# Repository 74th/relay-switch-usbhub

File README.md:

# Relay Switch USB 2.0 Hub

This is a USB hub with USB switching function using relays.

Many existing USB hubs with USB host switching function only allow 2-port switching, and I made this kit because we wanted a 4-port hub.
Since there are no USB hubs using USB Type-C available on the market, it is convenient to use USB Type-C.
Since I wanted to place the USB hub behind the display, we also added the ability to switch remotely using a Grove cable.

Usually a dedicated USB switching IC should be used for USB switching, but this is achieved by using a relay to switch between DM/DP. It works by me, so I am not guaranteeing that it works, but I am publishing it.

リレーを使った USB 切り替え機能付き USB ハブです。

既存の USB ホスト切り替え機能付き USB ハブでは、多くが 2 ポートしか切り替えられず、4 ポートが欲しかったため作りました。
USB Type-C を使った USB ハブは販売されていないため、USB Type-C が使えると便利です。
USB ハブはディスプレイの裏に置きたかったため、Grove ケーブルを使ってリモートから切り替えられる機能もつけました。

本来は USB 切り替えには USB 切り替え専用の IC を使うべきですが、これはリレーを使って DM/DP を切り替えることで実現しています。私の所では動作しているので、動作は保証しませんが、公開しています。

> Shop [BOOTH](https://74th.booth.pm/items/5080690)

## features

- Switch between 4 USB Hosts with Relay
- 4-port USB 2.0 hub using CH334
- MX compatible DIY keyboard switches can be used to switch between USB hosts
- Currently enabled USB host is indicated by LED color
- A Grove cable can be used to place a USB host switching switch at a remote location
- Power protection IC on both USB device and USB host side
- USB port next to LED for power supply
- All USB ports are Type-C

### Japanese

- リレーを使った USB ホスト切り替え機能
- CH334 を使った 4 ポート USB 2.0 ハブ
- USB ホストの切り替えスイッチには MX 互換自作キーボードスイッチが使える
- 現在有効な USB ホストを LED の色で表示する
- Grove ケーブルで、離れた位置に USB ホストを切り替えるスイッチを置くことができる
- USB デバイス、USB ホスト側の両方に電源保護 IC を搭載
- LED 横の USB ポートは電源供給用
- 全ての USB ポートは Type-C

## Repository Structure

- Relay USB Hub
  - PCB KiCad Data: [./main-pcb](./main-pcb)
  - Relay Control MCU Firmware(CH32V003F6P6): [./main-firmware](./main-firmware)
  - Case 3D Printer Model(WIP): [./case/case-bottom.stl](./case/case-bottom.stl)
- Button Unit Grove I2C
  - PCB KiCad Data: [./remote_switch-pcb](./remote_switch-pcb)
  - Button Unit MCU Firmware(CH32V003F6P6): [./remote_switch-firmware](./remote_switch-firmware)
  - Case 3D Printer Model(WIP): [./case/remote-bottom.stl](./case/remote-bottom.stl)

## About Using IC

- CH334R: USB 2.0 Hub controller IC
  - Product Site: https://www.wch-ic.com/products/CH334.html
  - Datasheet: https://www.wch-ic.com/downloads/CH334DS0_PDF.html
- CH32V003: Low Cost General Purpose MCU
  - Product Site: https://www.wch-ic.com/products/CH32V003.html
  - Datasheet: https://www.wch-ic.com/downloads/CH32V003DS0_PDF.html

## Relay USB Hub v1.0.1

- Semantics: [PDF](./main-pcb/relay_usb_switch_hub-v1.0.1-semantics.pdf) [Kicanvas](https://kicanvas.org/?github=https%3A%2F%2Fgithub.com%2F74th%2Frelay-switch-usbhub%2Fblob%2Fmain%2F1.0.1%2Fpcb%2Fusb_relay_hub.kicad_sch)
- PCB: [Kicanvas](https://kicanvas.org/?github=https%3A%2F%2Fgithub.com%2F74th%2Frelay-switch-usbhub%2Fblob%2Fmain%2F1.0.1%2Fpcb%2Fusb_relay_hub.kicad_pcb)

### BOM

| Reference          | Name                                             | Quantity |
| ------------------ | ------------------------------------------------ | -------- |
| C1, C3-C6, C8, C12 | Capacitor 0603 10uF                              | 7        |
| C2, C11            | Capacitor 0603 100nF                             | 2        |
| C7                 | NC                                               | 1        |
| C9, C10            | Capacitor 0603 20-22pF                           | 2        |
| CH2                | HY2.0 Socket SMD 4Pin - I2C                      | 1        |
| D1                 | RGBLED WS2812B                                   | 1        |
| D2-D5              | Fast Switching Diode SOD-123 1N4148W             | 4        |
| J1-J4              | USB Type-C Receptacle - USB Device               | 4        |
| J5                 | USB Type-C Receptacle - Power                    | 1        |
| J6-J9              | USB Type-C Receptacle - Com Host                 | 4        |
| K1-K4              | 5V 2 Form C Relay                                | 4        |
| R1-R10             | Register 0603 5.1kΩ                              | 10       |
| R11                | Register 0603 27Ω                                | 1        |
| R12                | Register 0603 10kΩ                               | 1        |
| R13-R20, R23-R26   | Register 0603 56kΩ                               | 12       |
| R21, R22           | Register 0603 1kΩ                                | 2        |
| SW1-SW4            | Cherry MX Compatible Switch or Kailh Choc Switch | 4        |
| U1-U4              | USB Power Protection IC SOT-23 CH213K            | 4        |
| U6                 | MCU LQFP48 WCH CH32V003F4P6                      | 1        |
| U7-U10             | USB Power Protection IC SOT-23-6L CH217K         | 4        |
| U11                | USB 2.0 Hub Controller QSOP-16 CH334R            | 1        |
| Y1                 | Crystal 3225 12MHz                               | 1        |

## Button Unit Grove v1.0.0

- Semantics: [PDF](./remote_switch-pcb/button_unit_grove_i2c-v1.0.0-semantics.pdf) [Kicanvas](https://kicanvas.org/?github=https%3A%2F%2Fgithub.com%2F74th%2Frelay-switch-usbhub%2Fblob%2Fbutton_unit_grove_i2c%2F1.0.0%2Fswitch-pcb%2Fswitch-pcb.kicad_sch)
- PCB: [Kicanvas](https://kicanvas.org/?github=https%3A%2F%2Fgithub.com%2F74th%2Frelay-switch-usbhub%2Fblob%2Fbutton_unit_grove_i2c%2F1.0.0%2Fswitch-pcb%2Fswitch-pcb.kicad_pcb)

### BOM

| Reference | Name                                             | Quantity |
| --------- | ------------------------------------------------ | -------- |
| C1        | Capacitor 0805 100nF                             | 1        |
| C2        | Capacitor 0805 10uF                              | 1        |
| CH1       | HY2.0 Socket SMD 4Pin - Grove I2C                | 1        |
| D1-D4     | RGBLED 3528 SK6812MINI-E                         | 4        |
| R1        | Register 0805 10kΩ                               | 1        |
| R2        | Register 0805 27Ω                                | 1        |
| SW1-SW4   | Cherry MX Compatible Switch or Kailh Choc Switch | 4        |
| U1        | MCU LQFP48 WCH CH32V003F4P6                      | 1        |

## License

MIT

日本では販売しないでいただけるとありがたいです。

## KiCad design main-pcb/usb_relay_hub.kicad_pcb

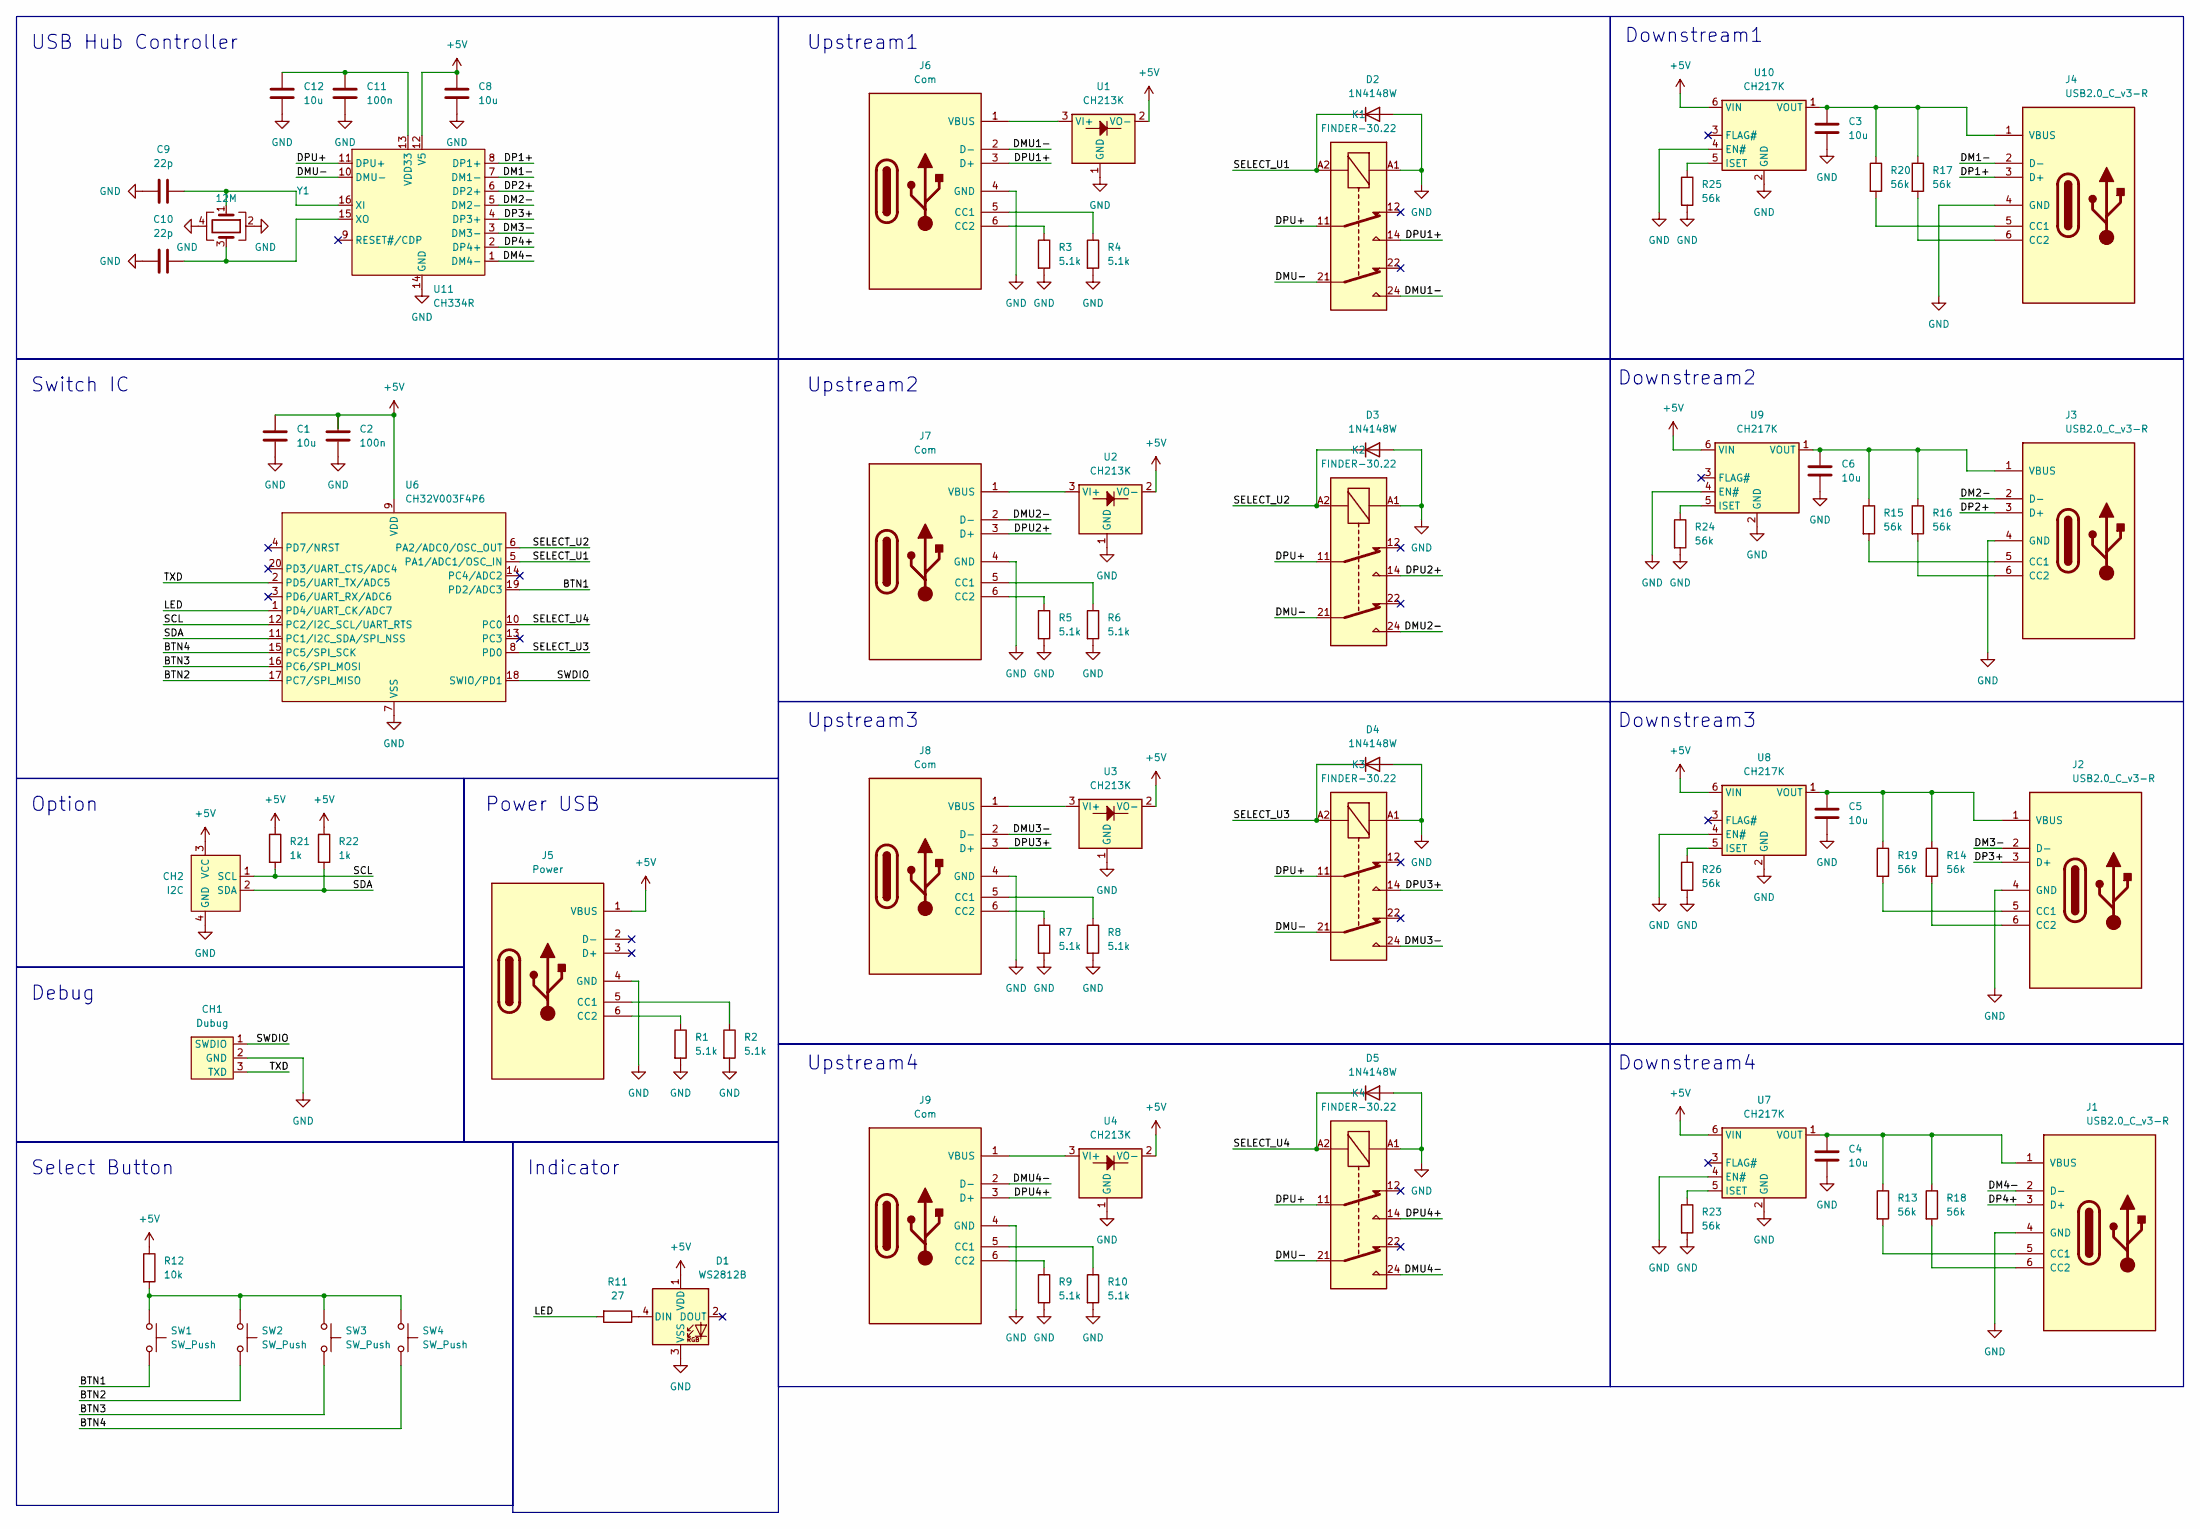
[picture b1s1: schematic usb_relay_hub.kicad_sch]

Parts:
C1, C3, C4, C5, C6, C8, C12: 10u; Capacitor_0603_1608
C2, C11: 100n; Capacitor_0603_1608
C9, C10: 22p; Capacitor_0603_1608
CH1: Dubug; CH32V003-DebugPort
CH2: I2C; HY2.0_Socket_SMD_4Pin
D1: WS2812B; LED_WS2812B_PLCC4_5.0x5.0mm_P3.2mm
D2, D3, D4, D5: 1N4148W; D_SOD-123
J1, J2, J3, J4: USB2.0_C_v3-R; USB-C-12-Pin-MidMount-ali-v5
J5: Power; USB-C-12-Pin-MidMount-ali-v5
J6, J7, J8, J9: Com; USB-C-12-Pin-MidMount-ali-v5
K1, K2, K3, K4: FINDER-30.22; Relay_DPDT_Finder_30.22
R1, R2, R3, R4, R5, R6, R7, R8, R9, R10: 5.1k; Register_0603_1608
R11: 27; Register_0603_1608
R12: 10k; Register_0603_1608
R13, R14, R15, R16, R17, R18, R19, R20, R23, R24, R25, R26: 56k; Register_0603_1608
R21, R22: 1k; Register_0603_1608
SW1, SW2, SW3, SW4: SW_Push; MXChocDirect_1Side_1.0u
U1, U2, U3, U4: CH213K; SOT-23
U6: CH32V003F4P6; TSSOP-20_4.4x6.5mm_P0.65mm
U7, U8, U9, U10: CH217K; SOT-23-6
U11: CH334R; QSOP-16_3.9x4.9mm_P0.635mm
Y1: 12M; Crystal_SMD_3225-4Pin_3.2x2.5mm_HandSoldering

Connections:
+5V: C1.1, C2.1, C8.1, CH2.3 (VCC), D1.1 (VDD), J5.1 (VBUS), R12.1, R21.1, R22.1, U1.2 (VO-), U2.2 (VO-), U3.2 (VO-), U4.2 (VO-), U6.9 (VDD), U7.6 (VIN), U8.6 (VIN), U9.6 (VIN), U10.6 (VIN), U11.12 (V5); also elsewhere on the board
/BTN1: SW1.2, U6.19 (PD2/ADC3)
/BTN2: SW2.2, U6.17 (PC7/SPI_MISO)
/BTN3: SW3.2, U6.16 (PC6/SPI_MOSI)
/BTN4: SW4.2, U6.15 (PC5/SPI_SCK)
/DM1-: J4.2 (D-), U11.7 (DM1-)
/DM2-: J3.2 (D-), U11.5 (DM2-)
/DM3-: J2.2 (D-), U11.3 (DM3-)
/DM4-: J1.2 (D-), U11.1 (DM4-)
/DMU1-: J6.2 (D-), K1.24
/DMU2-: J7.2 (D-), K2.24
/DMU3-: J8.2 (D-), K3.24
/DMU4-: J9.2 (D-), K4.24
/DMU-: K1.21, K2.21, K3.21, K4.21, U11.10 (DMU-)
/DP1+: J4.3 (D+), U11.8 (DP1+)
/DP2+: J3.3 (D+), U11.6 (DP2+)
/DP3+: J2.3 (D+), U11.4 (DP3+)
/DP4+: J1.3 (D+), U11.2 (DP4+)
/DPU1+: J6.3 (D+), K1.14
/DPU2+: J7.3 (D+), K2.14
/DPU3+: J8.3 (D+), K3.14
/DPU4+: J9.3 (D+), K4.14
/DPU+: K1.11, K2.11, K3.11, K4.11, U11.11 (DPU+)
/LED: R11.2, U6.1 (PD4/UART_CK/ADC7)
/SCL: CH2.1 (SCL), R21.2, U6.12 (PC2/I2C_SCL/UART_RTS)
/SDA: CH2.2 (SDA), R22.2, U6.11 (PC1/I2C_SDA/SPI_NSS)
/SELECT_U1: D2.1 (K), K1.A2, U6.5 (PA1/ADC1/OSC_IN)
/SELECT_U2: D3.1 (K), K2.A2, U6.6 (PA2/ADC0/OSC_OUT)
/SELECT_U3: D4.1 (K), K3.A2, U6.8 (PD0)
/SELECT_U4: D5.1 (K), K4.A2, U6.10 (PC0)
/SWDIO: CH1.1 (SWDIO), U6.18 (SWIO/PD1)
/TXD: CH1.3 (TXD), U6.2 (PD5/UART_TX/ADC5)
GND: C1.2, C2.2, C3.2, C4.2, C5.2, C6.2, C8.2, C9.2, C10.1, C11.2, C12.2, CH1.2 (GND), CH2.4 (GND), D1.3 (VSS), D2.2 (A), D3.2 (A), D4.2 (A), D5.2 (A), J1.4 (GND), J2.4 (GND), J3.4 (GND), J4.4 (GND), J5.4 (GND), J6.4 (GND), J7.4 (GND), J8.4 (GND), J9.4 (GND), K1.A1, K2.A1, K3.A1, K4.A1, R1.2, R2.2, R3.2, R4.2, R5.2, R6.2, R7.2, R8.2, R9.2, R10.2, R23.2, R24.2, R25.2, R26.2, U1.1 (GND), U2.1 (GND), U3.1 (GND), U4.1 (GND), U6.7 (VSS), U7.2 (GND), U7.4 (EN#), U8.2 (GND), U8.4 (EN#), U9.2 (GND), U9.4 (EN#), U10.2 (GND), U10.4 (EN#), U11.14 (GND), Y1.2, Y1.4; also elsewhere on the board
unnamed: D1.4 (DIN), R11.1
unnamed: J1.5 (CC1), R13.2
unnamed: J1.6 (CC2), R18.2
unnamed: C4.1, J1.1 (VBUS), R13.1, R18.1, U7.1 (VOUT)
unnamed: J2.5 (CC1), R19.2
unnamed: J2.6 (CC2), R14.2
unnamed: C5.1, J2.1 (VBUS), R14.1, R19.1, U8.1 (VOUT)
unnamed: J3.5 (CC1), R15.2
unnamed: J3.6 (CC2), R16.2
unnamed: C6.1, J3.1 (VBUS), R15.1, R16.1, U9.1 (VOUT)
unnamed: J4.5 (CC1), R20.2
unnamed: J4.6 (CC2), R17.2
unnamed: C3.1, J4.1 (VBUS), R17.1, R20.1, U10.1 (VOUT)
unnamed: J5.5 (CC1), R2.1
unnamed: J5.6 (CC2), R1.1
unnamed: J6.5 (CC1), R4.1
unnamed: J6.6 (CC2), R3.1
unnamed: J6.1 (VBUS), U1.3 (VI+)
unnamed: J7.5 (CC1), R6.1
unnamed: J7.6 (CC2), R5.1
unnamed: J7.1 (VBUS), U2.3 (VI+)
unnamed: J8.5 (CC1), R8.1
unnamed: J8.6 (CC2), R7.1
unnamed: J8.1 (VBUS), U3.3 (VI+)
unnamed: J9.5 (CC1), R10.1
unnamed: J9.6 (CC2), R9.1
unnamed: J9.1 (VBUS), U4.3 (VI+)
unnamed: R12.2, SW1.1, SW2.1, SW3.1, SW4.1
unnamed: R23.1, U7.5 (ISET)
unnamed: R26.1, U8.5 (ISET)
unnamed: R24.1, U9.5 (ISET)
unnamed: R25.1, U10.5 (ISET)
unnamed: C11.1, C12.1, U11.13 (VDD33)
unnamed: C9.1, U11.16 (XI), Y1.1
unnamed: C10.2, U11.15 (XO), Y1.3

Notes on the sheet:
Switch IC
Debug
Upstream2
Downstream1
Select Button
Power USB
Upstream1
Upstream4
Indicator
Downstream3
USB Hub Controller
Downstream4
Option
Downstream2
Upstream3

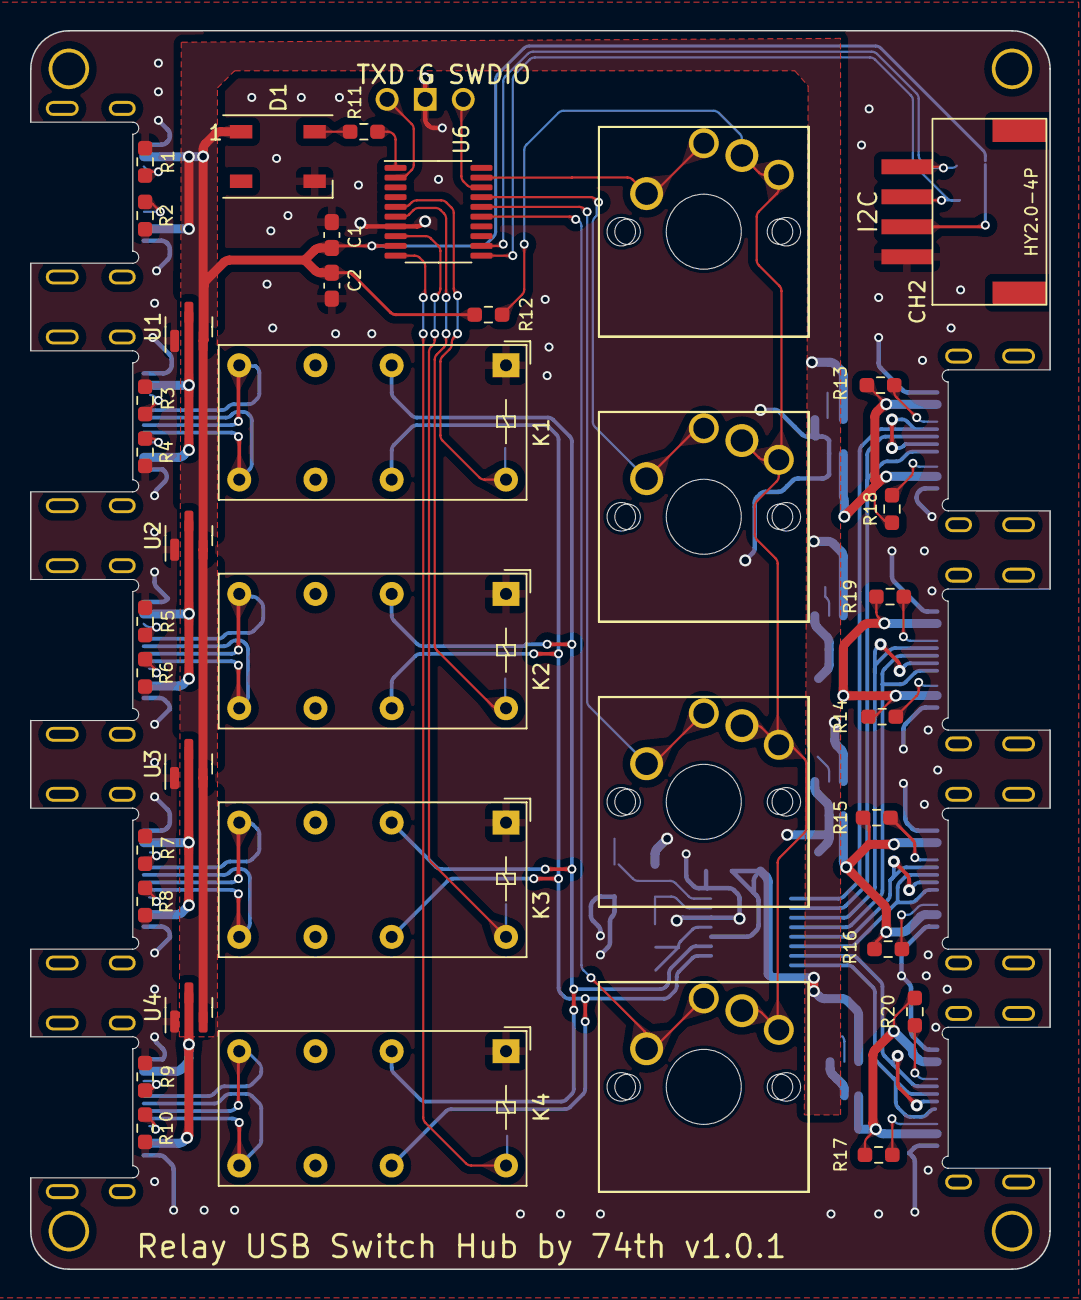
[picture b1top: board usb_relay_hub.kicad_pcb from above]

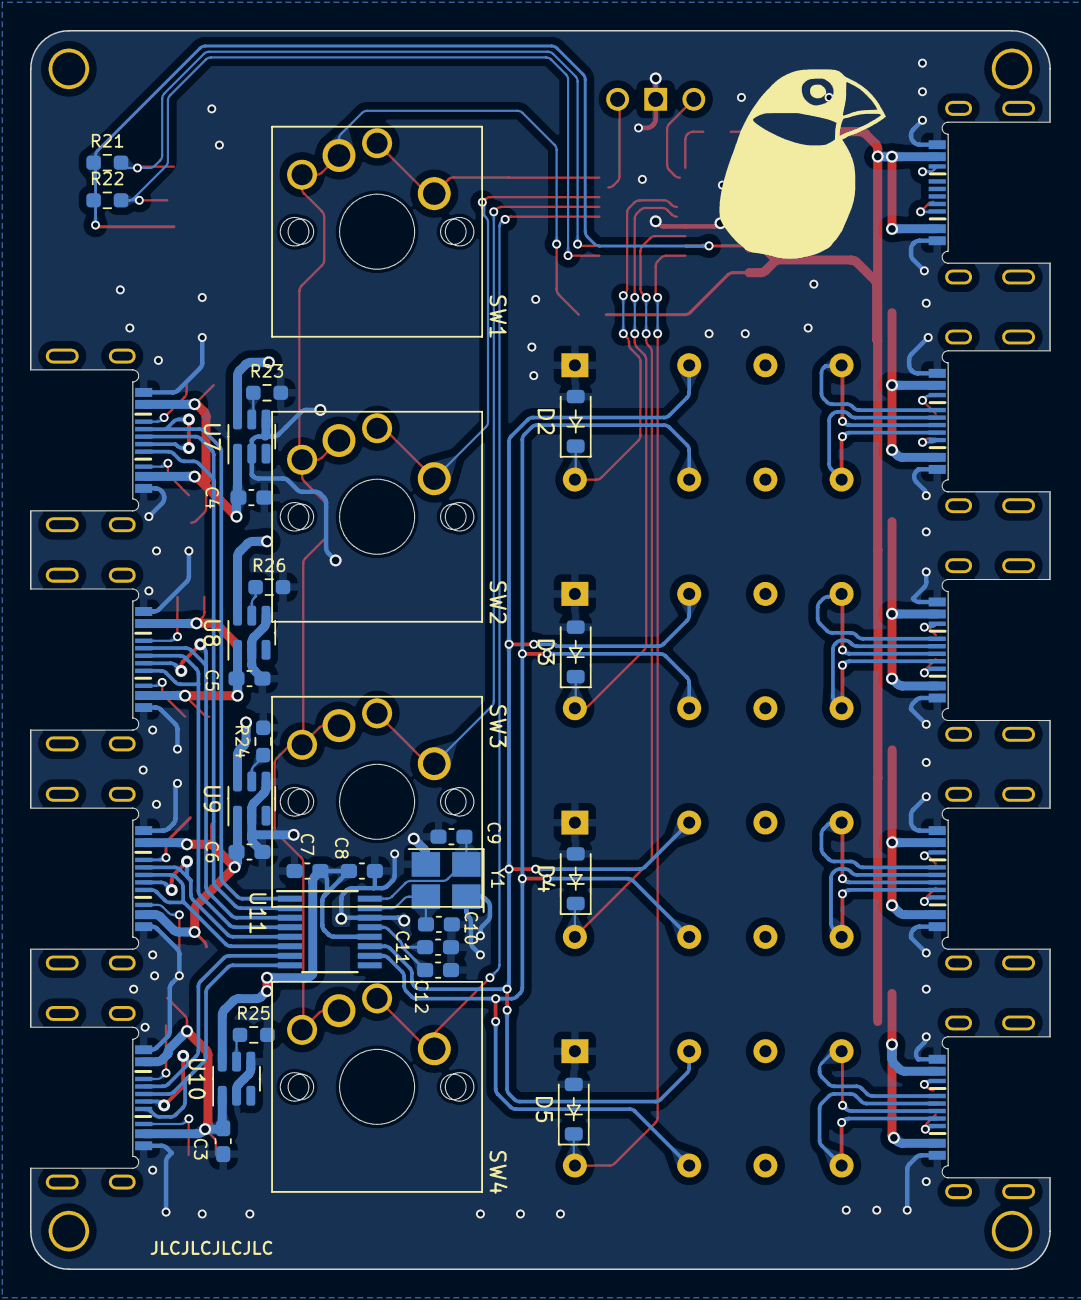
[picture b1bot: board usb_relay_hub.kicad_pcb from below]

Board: 2 copper layers, 67.9 x 82.5 mm, 77 parts (35 on the bottom side), 68 nets.

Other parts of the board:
C7: 100n; Capacitor_0603_1608
M1, M2, M3, M4: M2_v2

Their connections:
+5V: C7.1; also elsewhere on the board
GND: C7.2; also elsewhere on the board

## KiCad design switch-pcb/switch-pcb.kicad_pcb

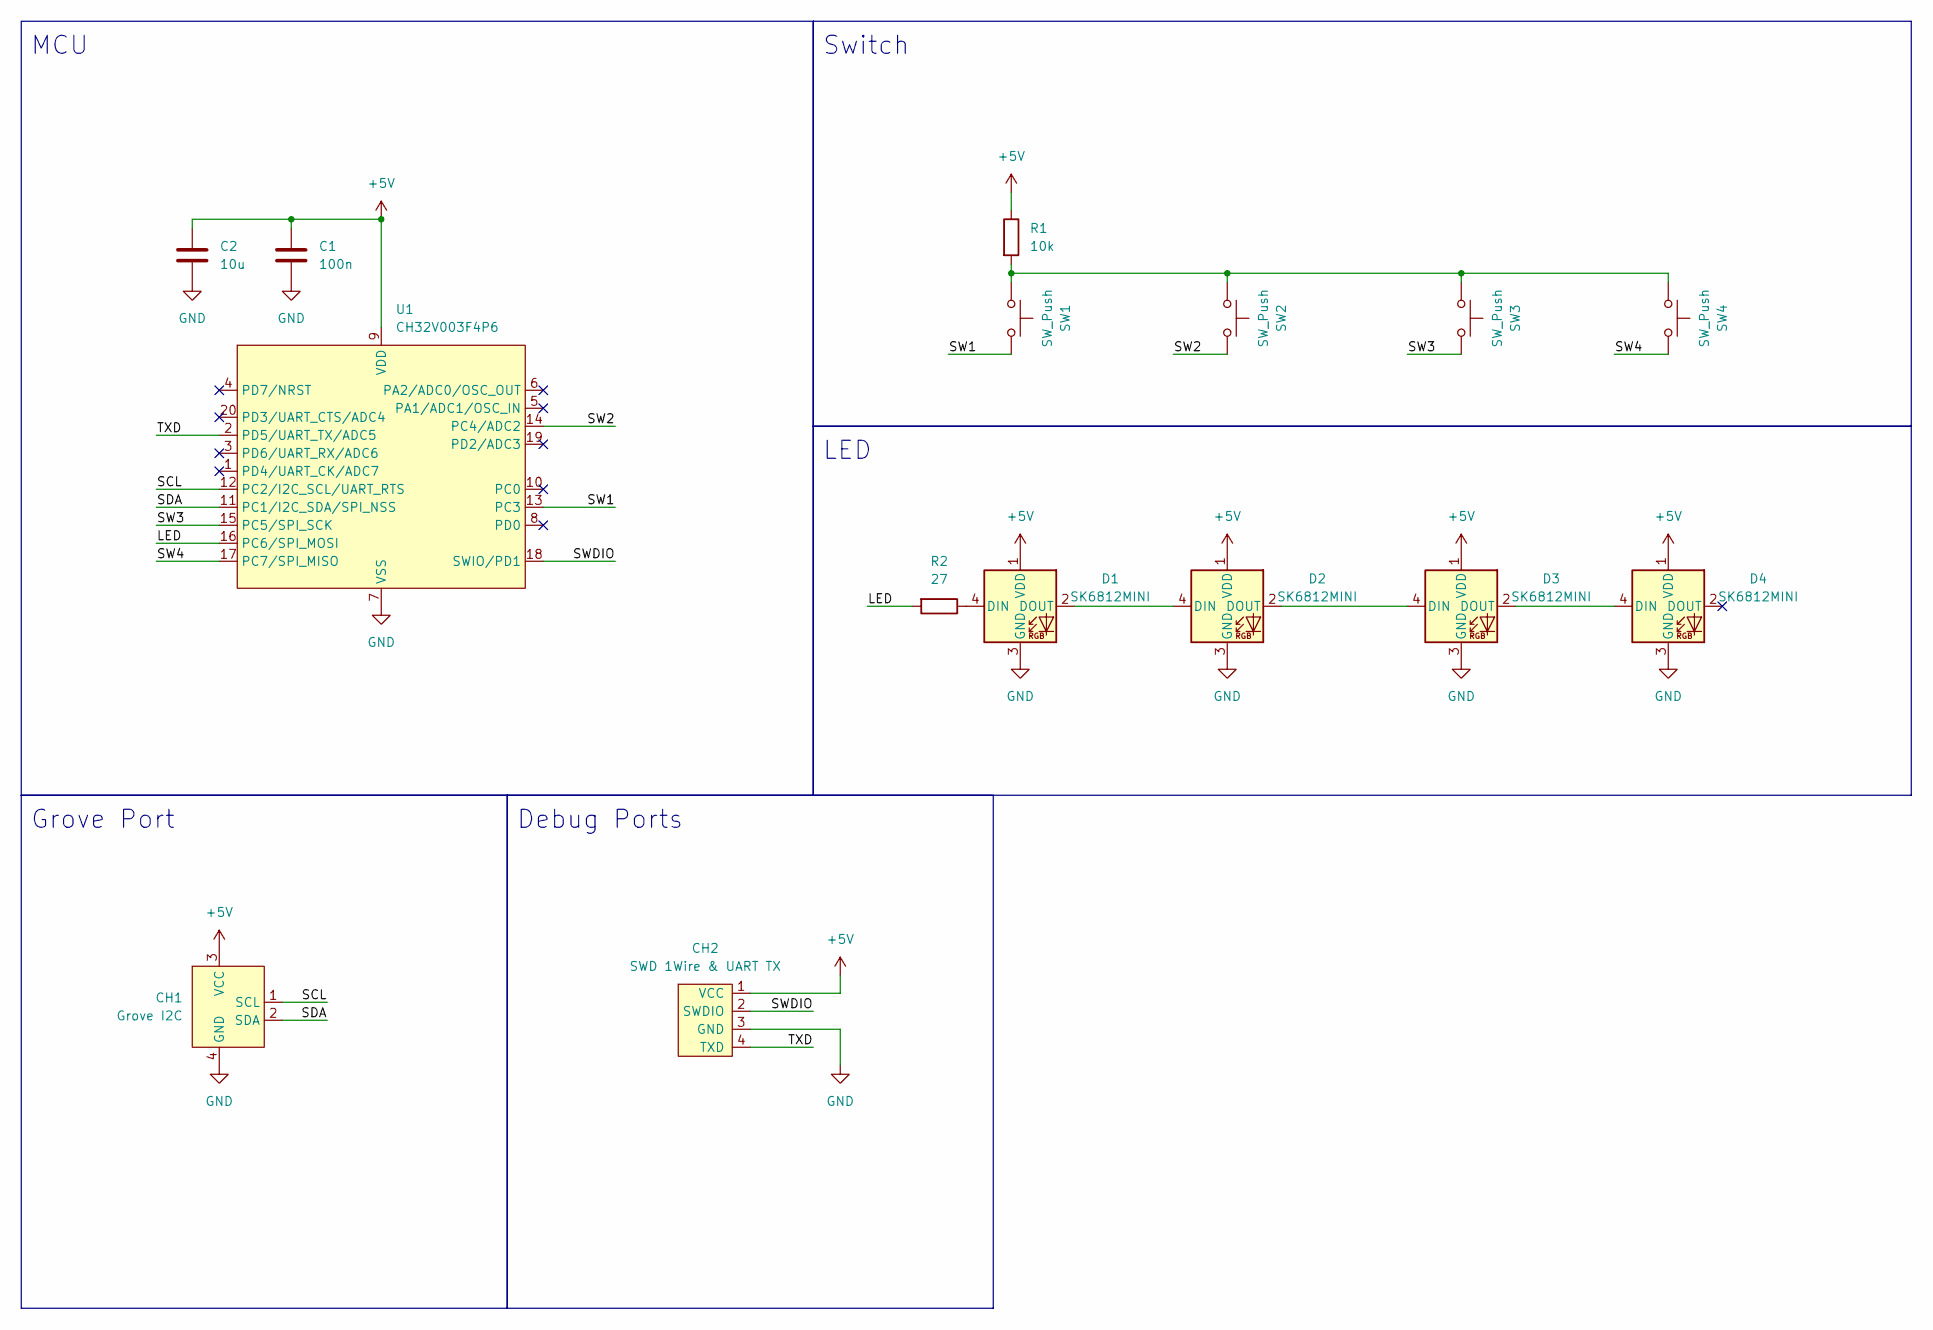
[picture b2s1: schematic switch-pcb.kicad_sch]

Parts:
C1: 100n; Capacitor_0805_2012
C2: 10u; Capacitor_0805_2012
CH1: Grove I2C; HY2.0_Socket_SMD_4Pin
CH2: SWD 1Wire & UART TX; CH32V003-DebugPort_with_vcc
D1, D2, D3, D4: SK6812MINI; YS-SK6812MINI-E-BACK-RIGHT
R1: 10k; Register_0805_2012
R2: 27; Register_0805_2012
SW1, SW2, SW3, SW4: SW_Push; MXChocDirect_1Side_1.0u
U1: CH32V003F4P6; TSSOP-20_4.4x6.5mm_P0.65mm

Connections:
+5V: C1.1, C2.1, CH1.3 (VCC), CH2.1 (VCC), D1.1 (VDD), D2.1 (VDD), D3.1 (VDD), D4.1 (VDD), R1.1, U1.9 (VDD)
/LED: R2.2, U1.16 (PC6/SPI_MOSI)
/SCL: CH1.1 (SCL), U1.12 (PC2/I2C_SCL/UART_RTS)
/SDA: CH1.2 (SDA), U1.11 (PC1/I2C_SDA/SPI_NSS)
/SW1: SW1.2, U1.13 (PC3)
/SW2: SW2.2, U1.14 (PC4/ADC2)
/SW3: SW3.2, U1.15 (PC5/SPI_SCK)
/SW4: SW4.2, U1.17 (PC7/SPI_MISO)
/SWDIO: CH2.2 (SWDIO), U1.18 (SWIO/PD1)
/TXD: CH2.4 (TXD), U1.2 (PD5/UART_TX/ADC5)
GND: C1.2, C2.2, CH1.4 (GND), CH2.3 (GND), D1.3 (GND), D2.3 (GND), D3.3 (GND), D4.3 (GND), U1.7 (VSS)
unnamed: D1.4 (DIN), R2.1
unnamed: D1.2 (DOUT), D2.4 (DIN)
unnamed: D2.2 (DOUT), D3.4 (DIN)
unnamed: D3.2 (DOUT), D4.4 (DIN)
unnamed: R1.2, SW1.1, SW2.1, SW3.1, SW4.1

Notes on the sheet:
LED
Debug Ports
Switch
MCU
Grove Port

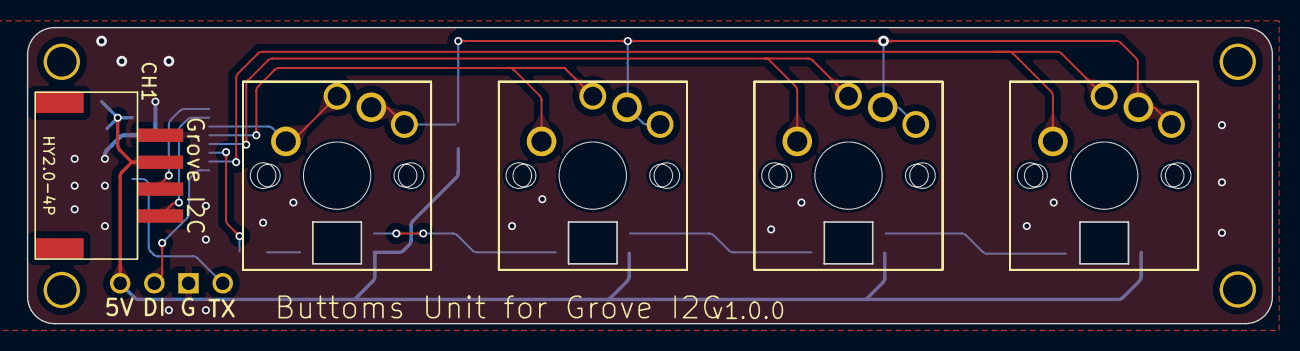
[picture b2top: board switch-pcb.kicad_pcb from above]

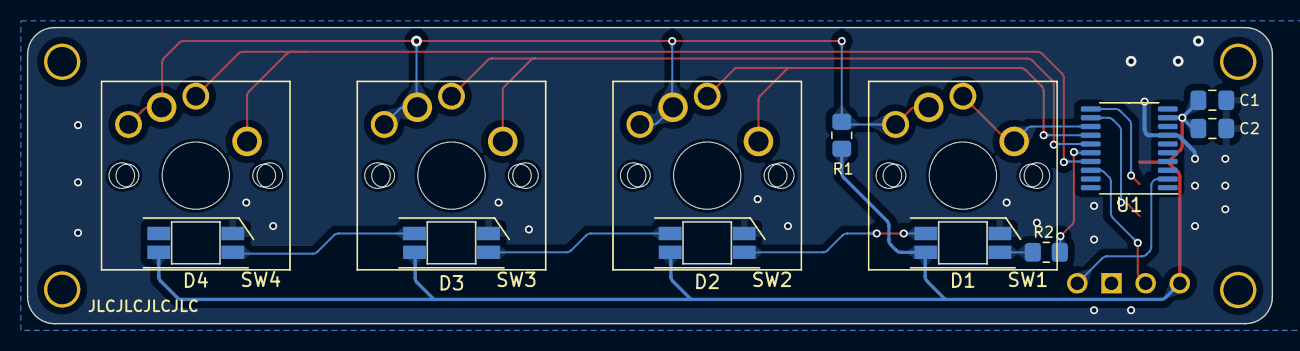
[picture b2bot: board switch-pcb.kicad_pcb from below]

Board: 2 copper layers, 92.5 x 22.0 mm, 19 parts (9 on the bottom side), 16 nets.

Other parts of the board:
M2-1, M2-1#2, M2-1#3, M2-1#4: M2_v2

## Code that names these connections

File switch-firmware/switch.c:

#include "ch32v003fun.h"
#include "ch32v003_GPIO_branchless.h"
#include "gpio_neopixel.h"
#include "switch.h"
#include <stdio.h>

#define I2C_SLAVE_ADDRESS 0x74
#define LOOP_MS 10
// #define LED_PIN GPIOv_from_PORT_PIN(GPIO_port_C, 3)
#define LED_PIN GPIOv_from_PORT_PIN(GPIO_port_D, 4)
#define SELECT_U1_PIN GPIOv_from_PORT_PIN(GPIO_port_A, 1)
#define SELECT_U2_PIN GPIOv_from_PORT_PIN(GPIO_port_A, 2)
#define SELECT_U3_PIN GPIOv_from_PORT_PIN(GPIO_port_D, 0)
#define SELECT_U4_PIN GPIOv_from_PORT_PIN(GPIO_port_C, 0)
#define BTN1_PIN GPIOv_from_PORT_PIN(GPIO_port_D, 2)
#define BTN2_PIN GPIOv_from_PORT_PIN(GPIO_port_C, 7)
#define BTN3_PIN GPIOv_from_PORT_PIN(GPIO_port_C, 6)
#define BTN4_PIN GPIOv_from_PORT_PIN(GPIO_port_C, 5)

void I2C1_EV_IRQHandler(void) __attribute__((interrupt));
void I2C1_ER_IRQHandler(void) __attribute__((interrupt));

void init_rcc(void)
{
    RCC->APB2PCENR |= RCC_APB2Periph_GPIOA | RCC_APB2Periph_GPIOC | RCC_APB2Periph_GPIOD;
    RCC->APB1PCENR |= RCC_APB1Periph_I2C1;
}

void init_i2c_slave(uint8_t address)
{
    // https://github.com/cnlohr/ch32v003fun/blob/master/examples/i2c_slave/i2c_slave.h

    // PC1 is SDA, 10MHz Output, alt func, open-drain
    GPIOC->CFGLR &= ~(0xf << (4 * 1));
    GPIOC->CFGLR |= (GPIO_Speed_10MHz | GPIO_CNF_OUT_OD_AF) << (4 * 1);

    // PC2 is SCL, 10MHz Output, alt func, open-drain
    GPIOC->CFGLR &= ~(0xf << (4 * 2));
    GPIOC->CFGLR |= (GPIO_Speed_10MHz | GPIO_CNF_OUT_OD_AF) << (4 * 2);

    // Reset I2C1 to init all regs
    RCC->APB1PRSTR |= RCC_APB1Periph_I2C1;
    RCC->APB1PRSTR &= ~RCC_APB1Periph_I2C1;

    I2C1->CTLR1 |= I2C_CTLR1_SWRST;
    I2C1->CTLR1 &= ~I2C_CTLR1_SWRST;

    // Set module clock frequency
    uint32_t prerate = 2000000; // I2C Logic clock rate, must be higher than the bus clock rate
    I2C1->CTLR2 |= (APB_CLOCK / prerate) & I2C_CTLR2_FREQ;

    // Enable interrupts
    I2C1->CTLR2 |= I2C_CTLR2_ITBUFEN;
    I2C1->CTLR2 |= I2C_CTLR2_ITEVTEN; // Event interrupt
    I2C1->CTLR2 |= I2C_CTLR2_ITERREN; // Error interrupt

    NVIC_EnableIRQ(I2C1_EV_IRQn); // Event interrupt
    NVIC_SetPriority(I2C1_EV_IRQn, 2 << 4);
    NVIC_EnableIRQ(I2C1_ER_IRQn); // Error interrupt
    // Set clock configuration
    uint32_t clockrate = 1000000;                                                    // I2C Bus clock rate, must be lower than the logic clock rate
    I2C1->CKCFGR = ((APB_CLOCK / (3 * clockrate)) & I2C_CKCFGR_CCR) | I2C_CKCFGR_FS; // Fast mode 33% duty cycle
    // I2C1->CKCFGR = ((APB_CLOCK/(25*clockrate))&I2C_CKCFGR_CCR) | I2C_CKCFGR_DUTY | I2C_CKCFGR_FS; // Fast mode 36% duty cycle
    // I2C1->CKCFGR = (APB_CLOCK/(2*clockrate))&I2C_CKCFGR_CCR; // Standard mode good to 100kHz

    // Set I2C address
    I2C1->OADDR1 = address << 1;

    // Enable I2C
    I2C1->CTLR1 |= I2C_CTLR1_PE;

    // Acknowledge the first address match event when it happens
    I2C1->CTLR1 |= I2C_CTLR1_ACK;
}

void I2C1_EV_IRQHandler(void)
{
    uint16_t STAR1, STAR2 __attribute__((unused));
    STAR1 = I2C1->STAR1;
    STAR2 = I2C1->STAR2;

    printf("EV STAR1: 0x%04x STAR2: 0x%04x\r\n", STAR1, STAR2);

    I2C1->CTLR1 |= I2C_CTLR1_ACK;

    if (STAR1 & I2C_STAR1_ADDR) // 0x0002
    {
        printf("ADDR\r\n");
        // 最初のイベント
        // read でも write でも必ず最初に呼ばれる
    }

    if (STAR1 & I2C_STAR1_RXNE) // 0x0040
    {
        printf("RXNE write event: \r\n");
        // 1byte 受信
        I2C1->DATAR;
    }

    if (STAR1 & I2C_STAR1_TXE) // 0x0080
    {
        // 1byte の read イベント（slave -> master）
        printf("TXE write event:\r\n");
        // 1byte 送信
        I2C1->DATAR = 0x00;
    }
}

void I2C1_ER_IRQHandler(void)
{
    uint16_t STAR1 = I2C1->STAR1;

    printf("ER STAR1: 0x%04x\r\n", STAR1);

    if (STAR1 & I2C_STAR1_BERR)           // 0x0100
    {                                     // Bus error
        I2C1->STAR1 &= ~(I2C_STAR1_BERR); // Clear error
    }

    if (STAR1 & I2C_STAR1_ARLO)           // 0x0200
    {                                     // Arbitration lost error
        I2C1->STAR1 &= ~(I2C_STAR1_ARLO); // Clear error
    }

    if (STAR1 & I2C_STAR1_AF)           // 0x0400
    {                                   // Acknowledge failure
        I2C1->STAR1 &= ~(I2C_STAR1_AF); // Clear error
    }
}

void init_gpio()
{
    GPIO_port_enable(GPIO_port_A);
    GPIO_port_enable(GPIO_port_C);
    GPIO_port_enable(GPIO_port_D);
    GPIO_pinMode(LED_PIN, GPIO_pinMode_O_pushPull, GPIO_Speed_10MHz);
    GPIO_pinMode(SELECT_U1_PIN, GPIO_pinMode_O_pushPull, GPIO_Speed_10MHz);
    GPIO_pinMode(SELECT_U2_PIN, GPIO_pinMode_O_pushPull, GPIO_Speed_10MHz);
    GPIO_pinMode(SELECT_U3_PIN, GPIO_pinMode_O_pushPull, GPIO_Speed_10MHz);
    GPIO_pinMode(SELECT_U4_PIN, GPIO_pinMode_O_pushPull, GPIO_Speed_10MHz);
    GPIO_pinMode(BTN1_PIN, GPIO_pinMode_I_pullDown, GPIO_Speed_10MHz);
    GPIO_pinMode(BTN2_PIN, GPIO_pinMode_I_pullDown, GPIO_Speed_10MHz);
    GPIO_pinMode(BTN3_PIN, GPIO_pinMode_I_pullDown, GPIO_Speed_10MHz);
    GPIO_pinMode(BTN4_PIN, GPIO_pinMode_I_pullDown, GPIO_Speed_10MHz);

    GPIO_digitalWrite_0(LED_PIN);
}

uint8_t usb1_color[3] = {0x00, 0x00, 0xF0};
uint8_t usb2_color[3] = {0x00, 0xF0, 0x00};
uint8_t usb3_color[3] = {0xF0, 0x00, 0x00};
uint8_t usb4_color[3] = {0x00, 0xF0, 0xF0};

void select_usb(int no)
{
    switch (no)
    {
    case 1:
        GPIO_digitalWrite(SELECT_U1_PIN, high);
        GPIO_digitalWrite(SELECT_U2_PIN, low);
        GPIO_digitalWrite(SELECT_U3_PIN, low);
        GPIO_digitalWrite(SELECT_U4_PIN, low);
        neopixel_write(GPIOD, GPIO_Pin_4, &usb1_color, 3);
        break;
    case 2:
        GPIO_digitalWrite(SELECT_U1_PIN, low);
        GPIO_digitalWrite(SELECT_U2_PIN, high);
        GPIO_digitalWrite(SELECT_U3_PIN, low);
        GPIO_digitalWrite(SELECT_U4_PIN, low);
        neopixel_write(GPIOD, GPIO_Pin_4, &usb2_color, 3);
        break;
    case 3:
        GPIO_digitalWrite(SELECT_U1_PIN, low);
        GPIO_digitalWrite(SELECT_U2_PIN, low);
        GPIO_digitalWrite(SELECT_U3_PIN, high);
        GPIO_digitalWrite(SELECT_U4_PIN, low);
        neopixel_write(GPIOD, GPIO_Pin_4, &usb3_color, 3);
        break;
    case 4:
        GPIO_digitalWrite(SELECT_U1_PIN, low);
        GPIO_digitalWrite(SELECT_U2_PIN, low);
        GPIO_digitalWrite(SELECT_U3_PIN, low);
        GPIO_digitalWrite(SELECT_U4_PIN, high);
        neopixel_write(GPIOD, GPIO_Pin_4, &usb4_color, 3);
        break;
    }
}

int read_pushed()
{
    int pushed = 0;
    if (GPIO_digitalRead(BTN1_PIN) == high)
    {
        pushed = 1;
    }
    if (GPIO_digitalRead(BTN2_PIN) == high)
    {
        pushed = 2;
    }
    if (GPIO_digitalRead(BTN3_PIN) == high)
    {
        pushed = 3;
    }
    if (GPIO_digitalRead(BTN4_PIN) == high)
    {
        pushed = 4;
    }

    return pushed;
}

int main()
{
    SystemInit();
    init_rcc();

    printf("initialize\r\n");

    // init_i2c_slave(I2C_SLAVE_ADDRESS);
    init_gpio();

    int current_usb_no = 1;
    select_usb(1);

    printf("initialize done\r\n");

    Delay_Ms(100);

    printf("neopixel test start\r\n");
    printf("UART CONF CTLR1:0x%08x CTLR2:0x%08x CTLR3:0x%08x\r\n", USART1->CTLR1, USART1->CTLR2, USART1->CTLR3);

    uint8_t data[3] = {0x00, 0x00, 0xF0};
    neopixel_write(GPIOD, GPIO_Pin_4, &usb1_color, 3);

    printf("neopixel test done\r\n");

    while (1)
    {
        int pushed_no = read_pushed();
        if (pushed_no > 0)
        {
            if (current_usb_no != pushed_no)
            {
                printf("pushed: %d\r\n", pushed_no);
                select_usb(pushed_no);
                current_usb_no = pushed_no;
            }
        }

        Delay_Ms(LOOP_MS);
    }
}

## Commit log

2023-08-13 select usb
2023-08-13 test neopixel
2023-08-15 pcb v1.0.0
2023-08-16 update case
2023-08-20 switch/1.0.0
2023-08-27 remote switch
2023-08-30 rename
2023-09-08 add photo
2023-09-09 update semantics
